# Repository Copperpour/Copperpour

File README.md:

<div align="center">

<h1> Copperpour</h1>

</div>

**AI-assisted PCB design for KiCad 10.** Copperpour is a native KiCad plugin — a single
Rust binary — that lets Claude and other AI assistants design schematics and PCBs
through the [Model Context Protocol](https://modelcontextprotocol.io) (MCP).

**257 tools across 23 on-demand toolsets.** Schematic capture, PCB layout and
routing, ERC/DRC, design-review audits, JLCPCB part search, reference
circuits, and a full manufacturing export pipeline — with bundled skills and agents
that teach Claude KiCad conventions out of the box.

> **Status: beta.** The core toolchain is tested and working, but this is a young
> release and it wants real-world mileage and review. Issues and PRs are welcome —
> see [CONTRIBUTING.md](CONTRIBUTING.md) and the
> [naming conventions](docs/NAMING_CONVENTIONS.md).
>
> **Formerly Konnect.** See [Why Copperpour exists](#why-copperpour-exists).

**New here?** [Install](#installation) in four steps, then follow
[Getting started](docs/GETTING_STARTED.md) through a first board.

## Why Copperpour exists

Copperpour keeps AI-assisted KiCad design open. It is the community-maintained
AGPL-3.0 fork of [Konnect](https://github.com/mixelpixx/Konnect), which went closed
source in October 2026, and Konnect was the successor to
[KiCAD-MCP-Server](https://github.com/mixelpixx/KiCAD-MCP-Server). Upgrading? See
[Migrating from Konnect](docs/MIGRATING_FROM_KONNECT.md).

- **One binary.** A single static Rust binary, a ~9 MB download, with no Node.js,
  Python or bindings to install. A tool call is a function call.
- **KiCad's IPC API.** Board edits go through KiCad 10's official IPC API in real
  time, with KiCad's own undo/redo, not the SWIG bindings KiCad is deprecating.
- **Safe schematic writes.** Its own S-expression engine edits `.kicad_sch` files
  with revision-checked atomic writes.
- **Small context.** A ~2K-token starter kit, with toolsets loaded on demand, instead
  of a ~23K-token catalogue on every listing.

## What it does

Instead of describing changes and applying them by hand, the AI works your project
directly:

- **Place and wire schematic components** — add resistors, ICs, connectors; wire them
  together by pin name
- **Lay out the PCB** — place, move, rotate, and route footprints in real time via
  KiCad's IPC API, with full undo/redo integration
- **Run design checks** — ERC, DRC, connectivity validation, decoupling audits,
  power-rail review, BOM health checks
- **Export production files** — Gerbers, drill, BOM, pick-and-place, 3D models, PDF
- **Search JLCPCB parts** — find in-stock components in a local catalog of about
  800k parts and suggest alternatives
- **Start from reference circuits** — USB-C, LDO, buck converter, STM32, I2C, LED
  templates with verified component values
- **Watch it happen** — a live schematic viewer auto-refreshes as the AI edits

The full tool catalog is documented in [tool-directory.md](tool-directory.md).

## How it works

| Layer | Mechanism |
|-------|-----------|
| Schematic editing | Direct `.kicad_sch` S-expression editing with atomic writes (no KiCad required) |
| PCB editing | KiCad 10 IPC API (NNG + protobuf) — real-time and undo-aware; single-footprint placement has a safe headless fallback |
| Specctra routing | Revision-bound Rust DSN export, local Freerouting MCP routing, and strict one-transaction SES import; an authenticated KiCad 10 native-export bridge is explicit opt-in |
| Exports & checks | `kicad-cli` subprocess (Gerber, PDF, ERC, DRC, …) |
| Transport | MCP JSON-RPC over stdio (default), or Streamable HTTP (`transport = "http"` / `"both"`) |

Explore the request path and safety boundaries in the
[interactive architecture diagrams](docs/ARCHITECTURE_DIAGRAMS.md).

## Installation

Requires **KiCad 10** on Windows, macOS or Linux.

### Step 1: Install the plugin into KiCad

1. Download the PCM package from
   [Releases](https://github.com/Copperpour/Copperpour/releases):
   `copperpour-pcm-v<version>.zip` carries Windows, macOS and Linux x86_64. The
   smaller `copperpour-pcm-v<version>-{windows,macos,linux}.zip` carry one OS each.
   The macOS build is universal (Apple Silicon and Intel). The other release
   archives are standalone server binaries; see
   [Advanced installation](#advanced-installation).
2. In KiCad: **Plugin and Content Manager → Install from File**, select the zip,
   restart KiCad.
3. Enable the IPC API: **Preferences → Plugins → Enable KiCad API**. Most PCB tools
   need KiCad running with the board open.

Verify: **PCB Editor → Tools → External Plugins** lists **Copperpour**.

Copperpour finds KiCad executables on `PATH` and in standard install locations,
including the macOS app bundle. Normal installations need no manual path settings.

### Step 2: Register the MCP server

Your AI client starts the server itself, over stdio, whenever it needs it; you never
run it by hand.

The PCM install puts the server binary at:

| OS | Server binary |
| --- | --- |
| Windows | `C:\Users\<YOU>\Documents\KiCad\10.0\3rdparty\plugins\com_github_copperpour_copperpour\bin\copperpour.exe` |
| macOS | `~/Documents/KiCad/10.0/3rdparty/plugins/com_github_copperpour_copperpour/bin/copperpour` |
| Linux | `~/.local/share/kicad/10.0/3rdparty/plugins/com_github_copperpour_copperpour/bin/copperpour` |

In the all-platforms package, `bin/copperpour` is a small `sh` launcher that runs
the macOS or Linux server beside it, so the path is the same in both packages.

**Claude Desktop**: add to `claude_desktop_config.json`
(`%APPDATA%\Claude\` on Windows, `~/Library/Application Support/Claude/` on macOS)
and restart Claude Desktop:

```json
{
  "mcpServers": {
    "copperpour": {
      "command": "C:\\Users\\<YOU>\\Documents\\KiCad\\10.0\\3rdparty\\plugins\\com_github_copperpour_copperpour\\bin\\copperpour.exe"
    }
  }
}
```

**Claude Code**: the same snippet in `.mcp.json` in your project root (see
[examples/](examples/)).

**Codex**:

```bash
codex mcp add copperpour -- /path/to/copperpour --client codex
```

**Other MCP clients**: register a stdio server with the binary as the command and
no arguments. Most clients take the same shape as Claude Desktop:

```json
{
  "mcpServers": {
    "copperpour": { "command": "/path/to/copperpour" }
  }
}
```

### Step 3: Install the skills (optional)

MCP registration is enough to receive short operating rules each session.
The server also serves its bundled skills and references on demand through
`get_guidance` and MCP resources, matching the running binary. No local skill
installation is needed for this guidance. Client support determines whether it
uses the instructions/resources; `get_guidance` is available before toolset loading.

Run `init` only if you want native skill discovery, locally editable skill files,
or Claude agents/hooks. Use the binary from Step 2 (PCM does not add it to `PATH`):

```bash
copperpour init                  # Claude: skills, agents and hooks
copperpour init --client codex   # Codex: skills under ~/.agents/skills
```

Re-run after upgrading Copperpour; it overwrites differing files, so back up any
you edited. See [Managing skills](#advanced-installation).

### Step 4: Verify

Ask your AI client for something read-only on an existing project:

> Show the project info for `~/kicad/myboard/myboard.kicad_pro`.

It should answer from `get_project_info` with the project name, its schematic and
PCB paths, and the KiCad version that wrote them. If Copperpour's tools don't show
up, or the call fails, ask for `get_installation_info`: it reports which binary is
serving, and whether it found `kicad-cli` and the KiCad API. See also
[Troubleshooting](#troubleshooting).

> [!TIP]
> **Installed? Continue with [Getting started →](docs/GETTING_STARTED.md)**
>
> It walks you from an empty project through schematic, PCB layout, design review and
> manufacturing files, with example prompts for each step.

Upgrading from Konnect? See [Migrating from Konnect](docs/MIGRATING_FROM_KONNECT.md) first.

## Advanced installation

You don't need any of this for a normal install. Expand a section when you need it.
For unusual KiCad locations or a custom API socket, see
[Manual configuration](docs/CONFIGURATION.md).

<details>
<summary><b>Standalone binary</b>: run the server without the KiCad plugin</summary>

The Releases page also has standalone server archives (`copperpour-v<version>-<target>`,
for example `aarch64-apple-darwin`). Unpack one and register the binary as in Step 2.

On macOS these files are not code-signed yet. If you downloaded one through a
browser, clear the quarantine flag first:

```bash
tar xzf copperpour-v*-aarch64-apple-darwin.tar.gz
xattr -d com.apple.quarantine ./copperpour
./copperpour --help
```

</details>

<details>
<summary><b>Build from source</b>: Rust, <code>protoc</code> and <code>cmake</code></summary>

You need [Rust](https://rustup.rs), `protoc` and `cmake`:

| System | Install the build tools |
| --- | --- |
| Windows | `choco install protoc cmake` |
| macOS | `brew install protobuf cmake` |
| Debian, Ubuntu | `apt install protobuf-compiler libprotobuf-dev cmake` |
| Fedora | `dnf install protobuf-compiler protobuf-devel cmake` |

Then build:

```bash
cargo build --release -p copperpour
```

The program is at `target/release/copperpour`, including the browser schematic
viewer. See [DEV.md](DEV.md) for build and test details.

For a build that makes no outbound connections, leave out the integrations:

```bash
cargo build --release -p copperpour --no-default-features
```

[DEV.md](DEV.md#build-features) lists what that build leaves out.

</details>

<details>
<summary><b>Managing skills</b>: check, update or remove what <code>copperpour init</code> installed</summary>

- `copperpour status` shows whether the installed skills match your Copperpour version.
- The server makes the same check once for each installed version. If the skills
  differ, it adds a one-line notice to its `initialize` instructions, and
  `get_installation_info` shows the result.
- Re-run `copperpour init` to update them.
- `copperpour uninstall` removes them. Add `--client codex` for Codex.

</details>

<details>
<summary><b>Autorouting</b>: route boards with Freerouting</summary>

Copperpour can autoroute a board with [Freerouting](https://freerouting.org):
`check_freerouting` checks the setup, then `export_specctra_dsn` →
`route_specctra_dsn` → `plan_specctra_ses_import` → `apply_specctra_ses` exports
the board, routes it, and imports the result.

Only fixed straight tracks and through vias are supported so far; boards with arcs,
zones or unlocked routing are refused before anything changes.

Optionally, KiCad 10 can export the board itself instead of Copperpour's own
exporter: enable the **native Specctra bridge** in Copperpour's settings dialog and
set `native_bridge_mode` to `"prefer"` (fall back to Copperpour's exporter) or
`"require"` (fail if native export is unavailable or invalid). Native export is
attempted before Rust-only outline checks; shared import-safety limits still apply.
See [the mode contract](docs/KICAD_INTEGRATION.md).

</details>

## Schematic viewer

The `open_schematic_viewer` MCP tool starts a browser viewer that refreshes when
saved schematic files change. Pass the root sheet of a hierarchy to get a sheet
selector. The tool returns a private loopback URL and asks the OS to open it;
use `open_browser: false` to return the URL without opening a browser. If opening
a browser fails, the service remains available at the returned URL.

The server reuses one viewer per canonical root schematic for the MCP server
context. Keep the URL private: its fragment contains the launch credential.
Stdio disconnect or HTTP server shutdown ends the viewer; disconnecting a client
from the stateless HTTP transport does not stop it. The display reflects saved
files, including agent edits, rather than unsaved KiCad changes. Pan by dragging,
zoom with the wheel, press `0` to fit or `R` to refresh, and use the toolbar to
select sheets or launch KiCad. Browser mode is bound to its root at launch and
has no file-drop control. It needs `kicad-cli`, using the server's configured path
or normal discovery, and a browser; no Tauri runtime is needed.

The browser viewer is embedded in the MCP server and PCM package. No separate
viewer executable or GTK/WebKit/WebView build is needed. The standalone
`schematic-viewer` command has been retired; use `open_schematic_viewer` instead.
See the [retirement migration](docs/api-migrations/retire-standalone-viewer.md) and
[browser response contract](docs/api-migrations/browser-viewer-mcp.md).

## Requirements

- KiCad 10 on Windows, macOS or Linux. Windows is the most tested; macOS and Linux
  have had less hands-on testing.
- `kicad-cli`, which ships with KiCad, for exports, ERC and DRC.
- For most PCB tools, KiCad running with the board open and its API enabled. A few
  placement tools [fall back to the closed board file](docs/TROUBLESHOOTING.md#pcb-tools-return-kicad-must-be-running-with-the-board-loaded).

## License

Copperpour is licensed under the **[GNU AGPL-3.0](LICENSE)**.

If you're a hobbyist, student, freelancer, or open-source project: **use it freely,
no strings attached.** Design boards, ship them, sell them.

If you're a business: using it in-house is free too. The AGPL's conditions apply when
you distribute Copperpour, or let outside users interact with a modified copy over a
network. Then they get its source under the same license.

## Troubleshooting

Start with `get_installation_info`: it reports which binary is serving, and whether it
found `kicad-cli` and the KiCad API. The common problems:

- [Plugin doesn't appear in KiCad](docs/TROUBLESHOOTING.md#plugin-doesnt-appear-in-kicad)
- [PCB tools return "KiCAD must be running with the board loaded"](docs/TROUBLESHOOTING.md#pcb-tools-return-kicad-must-be-running-with-the-board-loaded)
- [A schematic write is blocked by a KiCad editor lock](docs/TROUBLESHOOTING.md#a-schematic-write-is-blocked-by-a-kicad-editor-lock)
- ["kicad-cli not found"](docs/TROUBLESHOOTING.md#kicad-cli-not-found)
- [Tools don't appear after `load_toolset`](docs/TROUBLESHOOTING.md#tools-dont-appear-after-load_toolset)

[docs/TROUBLESHOOTING.md](docs/TROUBLESHOOTING.md) covers the rest, including socket
setup and transaction recovery.

## Support

- Issues & feature requests: [GitHub Issues](https://github.com/Copperpour/Copperpour/issues)
- Contributing: [CONTRIBUTING.md](CONTRIBUTING.md)

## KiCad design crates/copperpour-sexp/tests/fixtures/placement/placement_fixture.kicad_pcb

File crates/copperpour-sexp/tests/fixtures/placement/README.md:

# Placement fixture — provenance

Purpose-built project for the placement, test-point, and voltage-drop
work: an SOIC-8 op-amp (U1) with two 0402 decouplers (C1, C2) on
VCC/GND, a 10k resistor (R1, rotated 90), a 4-pin header (J1), a 0.8mm-
pitch BGA fanout target (U2, board-only), two through-hole test points
(TP1, TP2, board-only), a 60x45mm outline, and a three-segment routed
VCC track run.

Provenance: the schematic was authored through Copperpour's own schematic
tools; the BOARD file's serialization is KiCad's — every footprint was
added by `update_pcb_from_schematic` / `place_component` over live IPC
into a running pcbnew 10.0.5, tracks by `route_trace`, and the file was
written by KiCad's own save (`save_project`), twice. Fields, pad nets
(VCC / GND / /SIG_IN), courtyards, and 3D references are exactly what
KiCad emits.

Regenerating: scripts build_t07b.py (schematic phase, KiCad closed) and
build_t07_board.py (board phase, pcbnew open) in the session scratchpad
that produced this; the flow is ordinary Copperpour tool calls and can be
re-derived from this README's description.

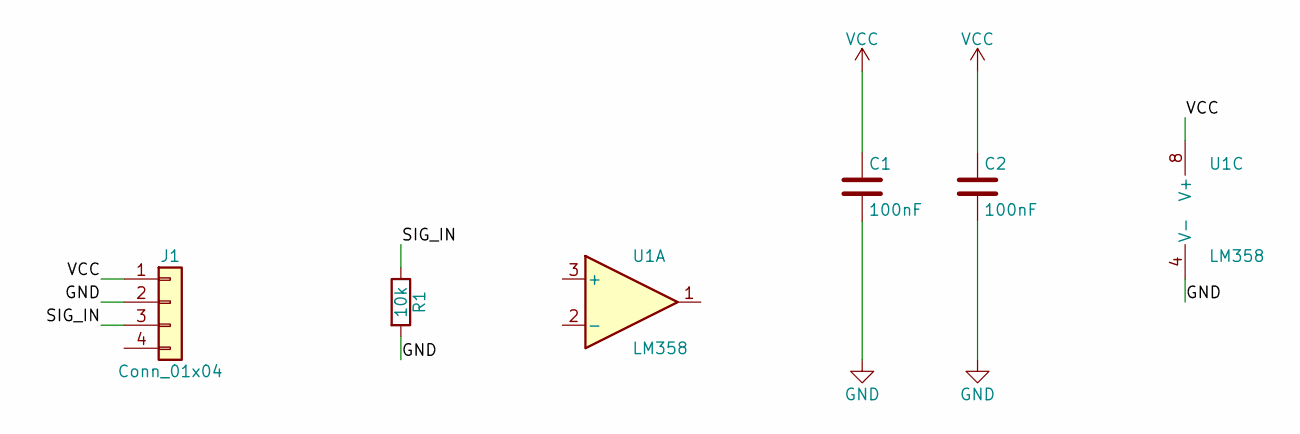
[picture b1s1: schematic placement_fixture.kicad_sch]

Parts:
C1, C2: 100nF; C_0402_1005Metric
J1: Conn_01x04; PinHeader_1x04_P2.54mm_Vertical
R1: 10k; R_0402_1005Metric
U1: LM358; SOIC-8_3.9x4.9mm_P1.27mm

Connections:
/SIG_IN: J1.3, R1.1
GND: C1.2, C2.2, J1.2, R1.2, U1.4 (V-)
VCC: C1.1, C2.1, J1.1, U1.8 (V+)

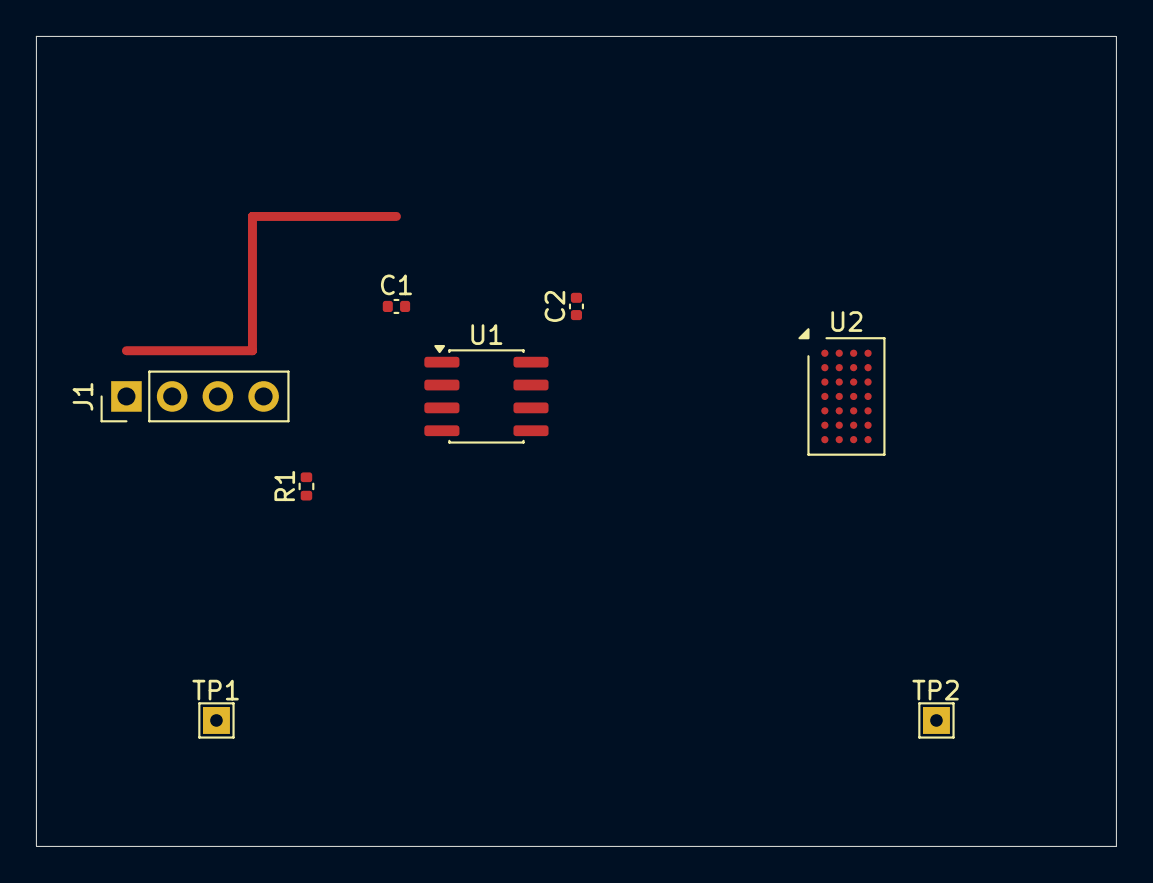
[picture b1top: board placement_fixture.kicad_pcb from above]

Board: 2 copper layers, 60.0 x 45.0 mm, 8 parts (0 on the bottom side), 3 nets.

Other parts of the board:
TP1, TP2: TestPoint_THTPad_1.5x1.5mm_Drill0.7mm
U2: Analog_BGA-28_4x6.25mm_Layout4x7_P0.8mm

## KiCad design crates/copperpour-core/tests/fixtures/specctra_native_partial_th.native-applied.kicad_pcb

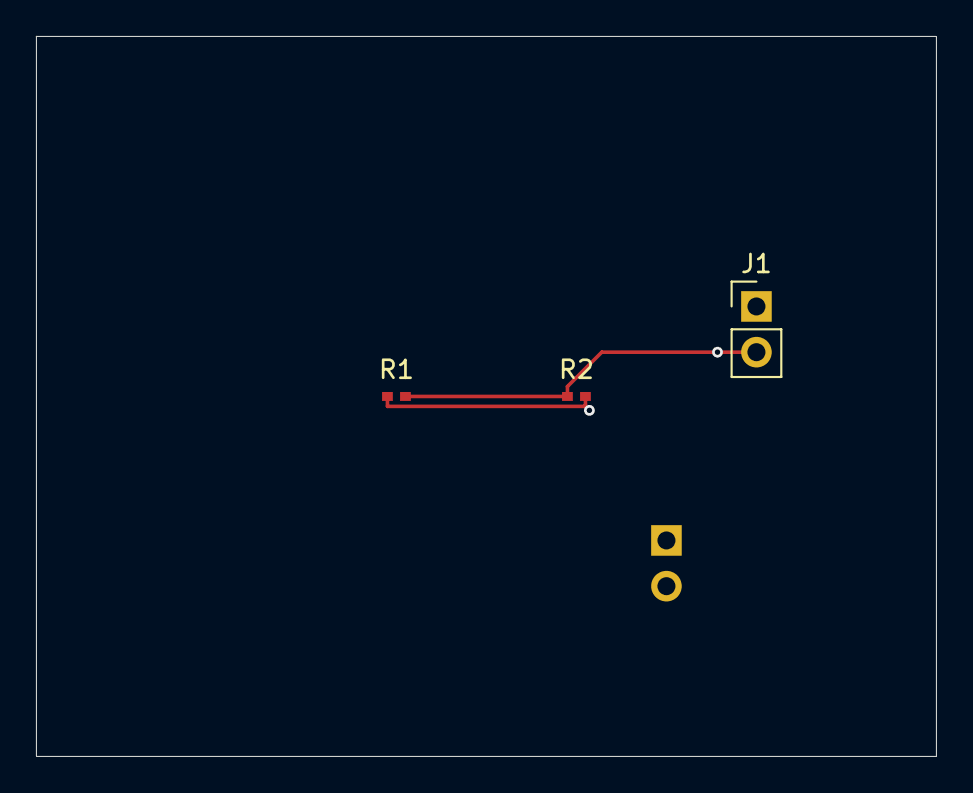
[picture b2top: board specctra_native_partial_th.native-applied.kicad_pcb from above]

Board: 4 copper layers, 50.0 x 40.0 mm, 4 parts (1 on the bottom side), 2 nets.

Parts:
J1: PinHeader_1x02_P2.54mm_Vertical
J2: PinHeader_1x02_P2.54mm_Horizontal
R1: 10k; R_0402
R2: 4.7k; R_0402

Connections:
GND: J1.2, J2.2, R1.2, R2.1
VCC: J1.1, J2.1, R1.1, R2.2

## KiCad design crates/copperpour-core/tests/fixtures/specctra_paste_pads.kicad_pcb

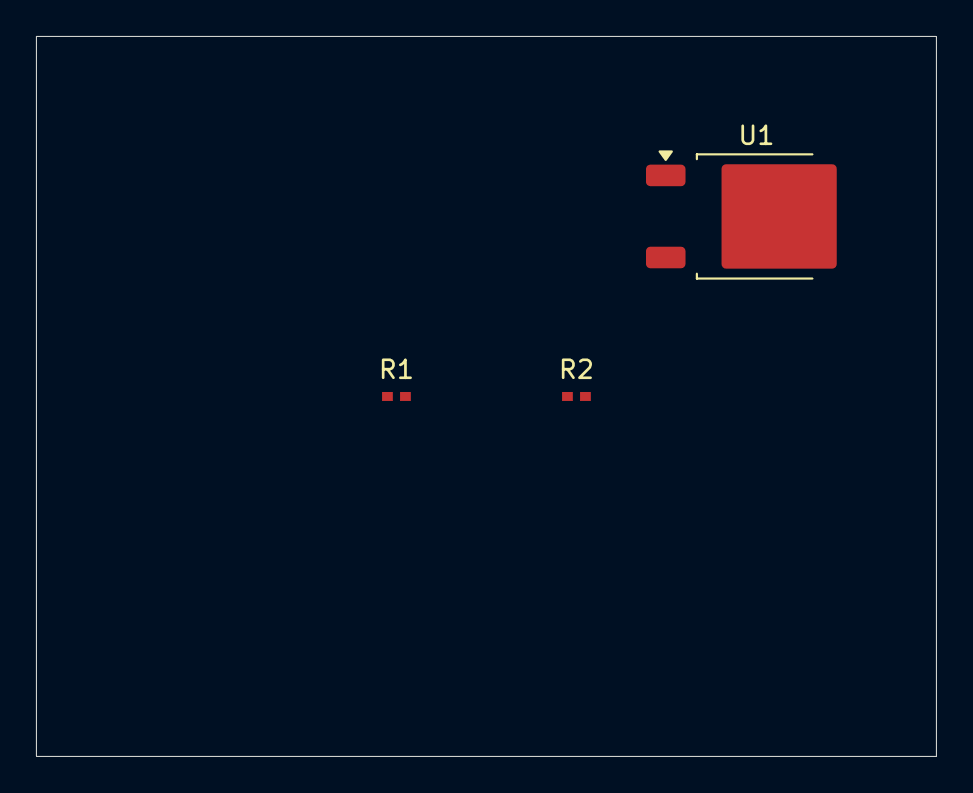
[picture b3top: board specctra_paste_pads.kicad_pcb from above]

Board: 2 copper layers, 50.0 x 40.0 mm, 4 parts (1 on the bottom side), 2 nets, no tracks yet.

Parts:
R1: 10k; R_0402
R2: 4.7k; R_0402
U1: TO-252-2
U2: TO-263-2

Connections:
GND: R1.2, R2.1, U1.2, U2.2
VCC: R1.1, R2.2, U1.1, U2.1

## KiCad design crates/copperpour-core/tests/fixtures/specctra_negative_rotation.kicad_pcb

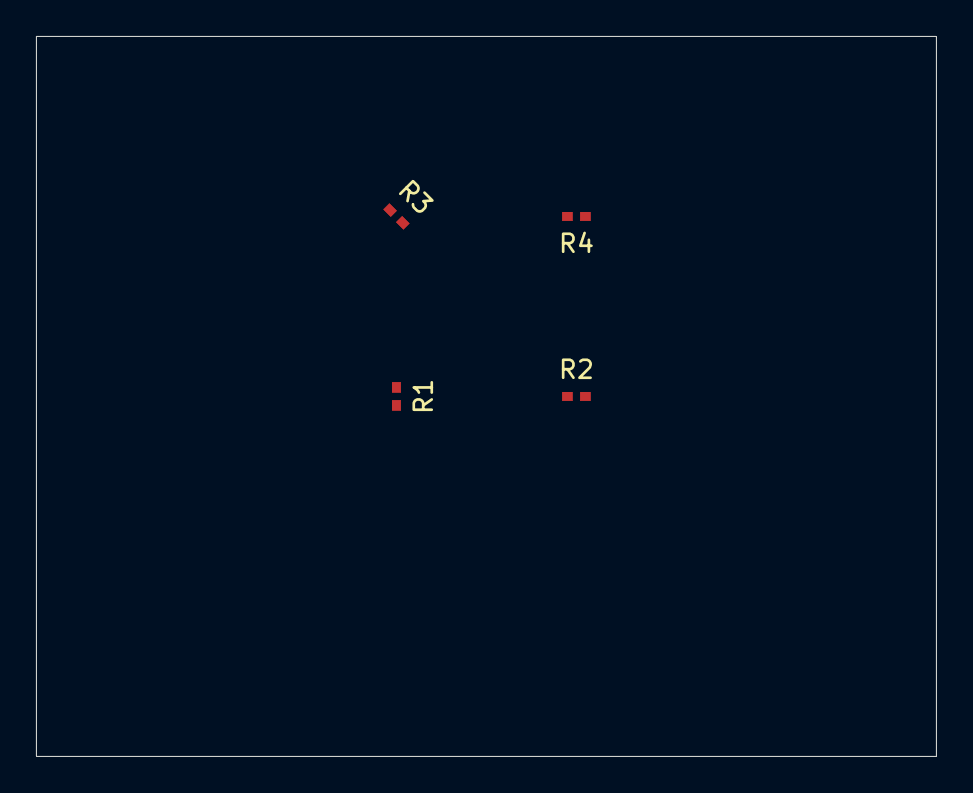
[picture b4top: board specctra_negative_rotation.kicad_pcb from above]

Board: 2 copper layers, 50.0 x 40.0 mm, 4 parts (0 on the bottom side), 2 nets, no tracks yet.

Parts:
R1: 10k; R_0402
R2, R3, R4: 4.7k; R_0402

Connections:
GND: R1.2, R2.1, R3.2, R4.1
VCC: R1.1, R2.2, R3.1, R4.2

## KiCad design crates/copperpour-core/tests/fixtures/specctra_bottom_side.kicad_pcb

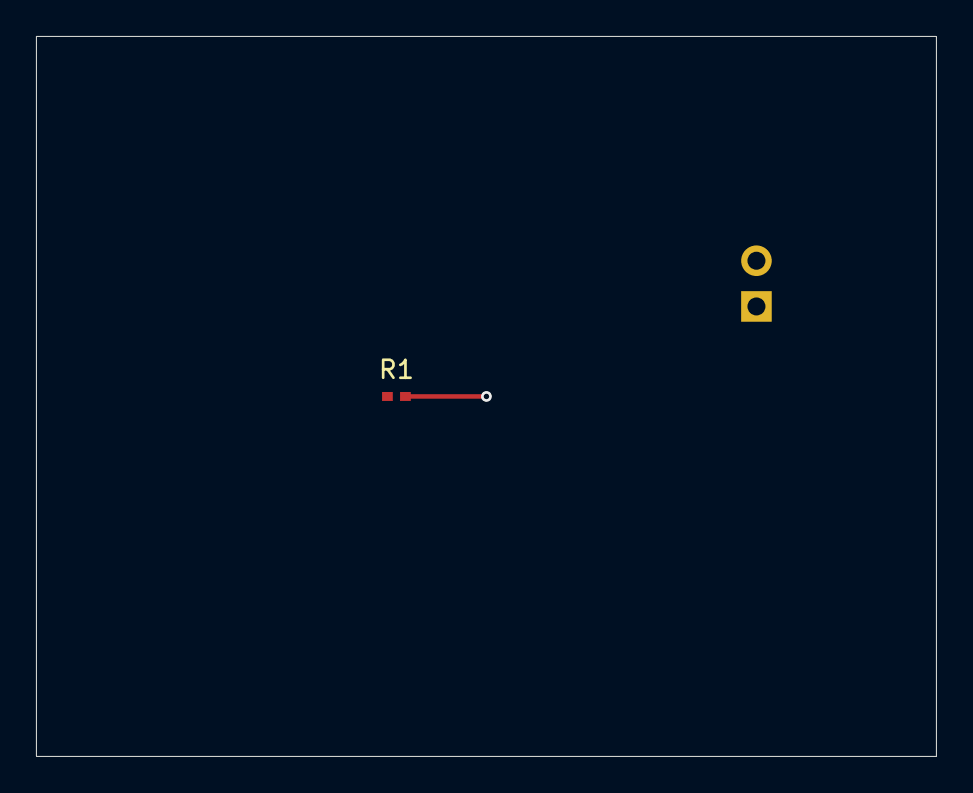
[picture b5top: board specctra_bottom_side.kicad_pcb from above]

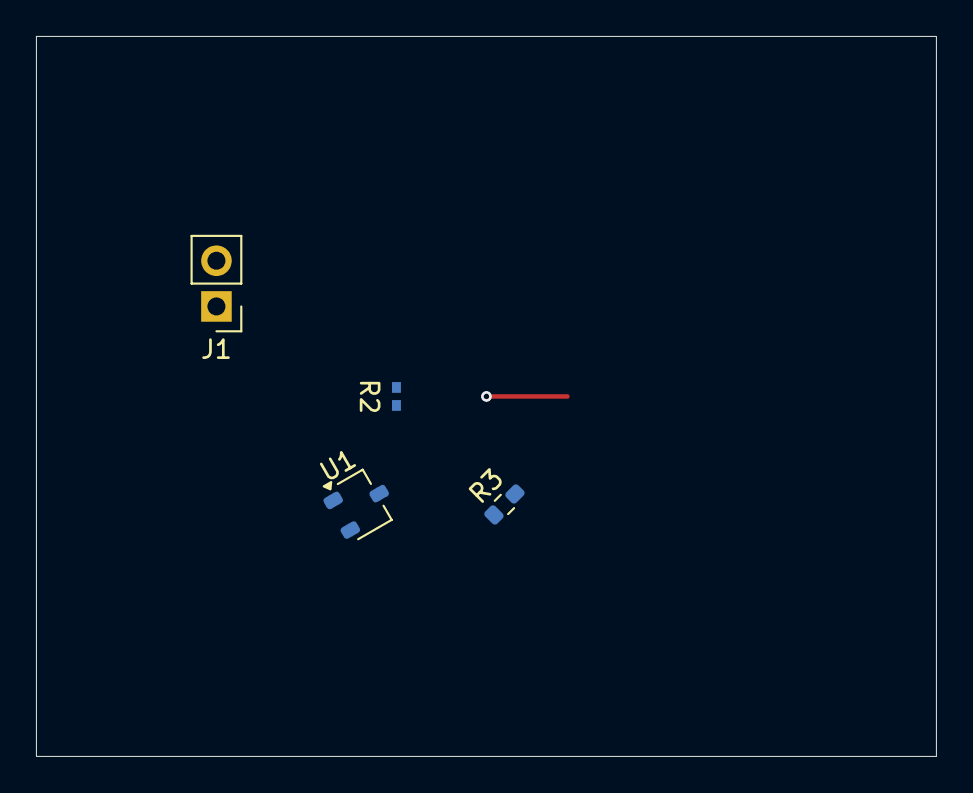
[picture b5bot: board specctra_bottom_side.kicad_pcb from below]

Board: 4 copper layers, 50.0 x 40.0 mm, 5 parts (4 on the bottom side), 2 nets.

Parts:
J1: PinHeader_1x02_P2.54mm_Vertical
R1: 10k; R_0402
R2: 4.7k; R_0402
R3: R_0603_1608Metric
U1: SOT-23W

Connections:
GND: J1.2, R1.2, R2.1, R3.2, U1.2
VCC: J1.1, R1.1, R2.2, R3.1, U1.1, U1.3

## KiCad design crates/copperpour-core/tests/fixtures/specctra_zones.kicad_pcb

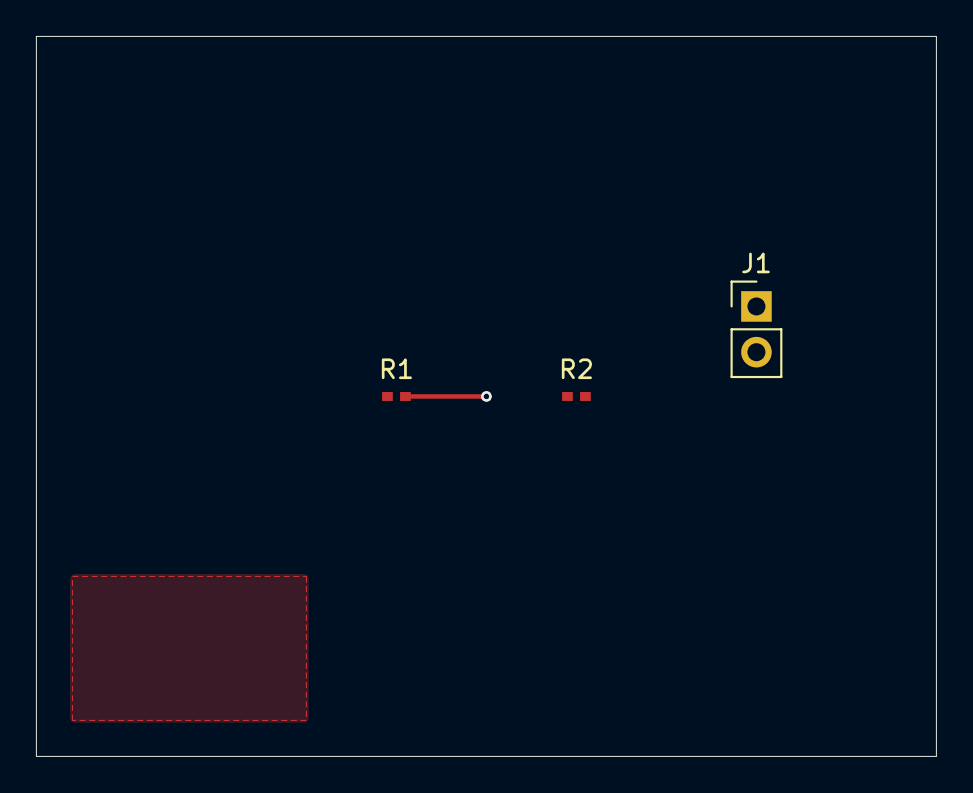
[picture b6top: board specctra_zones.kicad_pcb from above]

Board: 4 copper layers, 50.0 x 40.0 mm, 3 parts (0 on the bottom side), 2 nets.

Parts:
J1: PinHeader_1x02_P2.54mm_Vertical
R1: 10k; R_0402
R2: 4.7k; R_0402

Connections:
GND: J1.2, R1.2, R2.1
VCC: J1.1, R1.1, R2.2
